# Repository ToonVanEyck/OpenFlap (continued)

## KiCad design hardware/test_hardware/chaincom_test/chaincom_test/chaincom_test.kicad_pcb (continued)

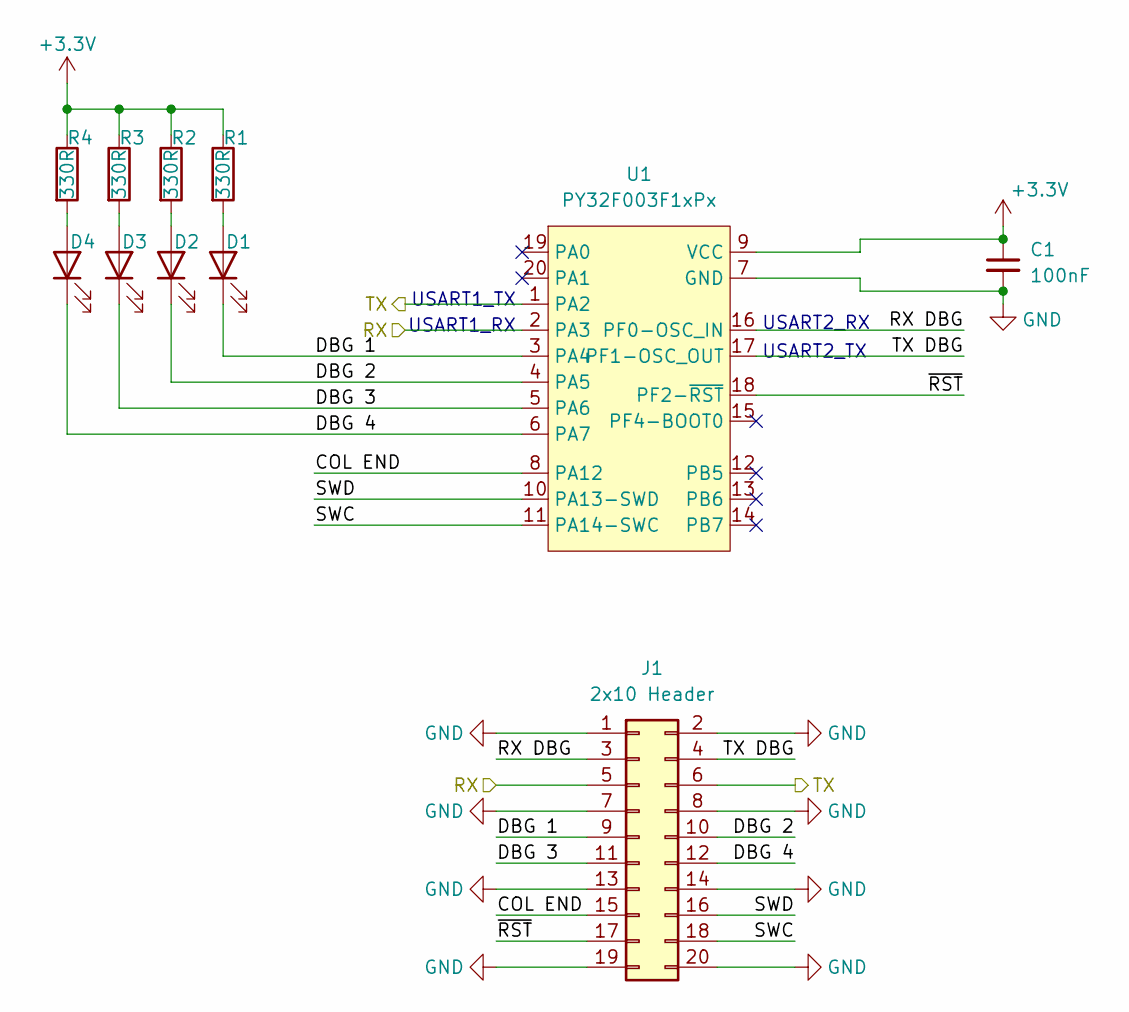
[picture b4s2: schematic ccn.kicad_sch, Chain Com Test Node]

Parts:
C1: 100nF; C_0805_2012Metric
D1: XL-1608UBC-06A; LED_0603_1608Metric; LCSC C7371904
D2: XL-1608SYGC-06; LED_0603_1608Metric; LCSC C965805
D3: XL-1608UOC-06; LED_0603_1608Metric; LCSC C965800
D4: XL-1608SURC-06; LED_0603_1608Metric; LCSC C965799
J1: 2x10 Header; PinHeader_2x10_P2.54mm_Vertical
R1, R2, R3, R4: 330R; R_0805_2012Metric
U1: PY32F003F1xPx; TSSOP-20_4.4x6.5mm_P0.65mm; LCSC C5379864

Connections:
+3.3V: C1.1, R1.1, R2.1, R3.1, R4.1, U1.9 (VCC); also elsewhere on the board
/Chain Com Node 1/COL END: J1.15, U1.8 (PA12)
/Chain Com Node 1/DBG 1: D1.1 (K), J1.9, U1.3 (PA4)
/Chain Com Node 1/DBG 2: D2.1 (K), J1.10, U1.4 (PA5)
/Chain Com Node 1/DBG 3: D3.1 (K), J1.11, U1.5 (PA6)
/Chain Com Node 1/DBG 4: D4.1 (K), J1.12, U1.6 (PA7)
/Chain Com Node 1/RX DBG: J1.3, U1.16 (PF0-OSC_IN)
/Chain Com Node 1/SWC: J1.18, U1.11 (PA14-SWC)
/Chain Com Node 1/SWD: J1.16, U1.10 (PA13-SWD)
/Chain Com Node 1/TX: J1.6, U1.1 (PA2); also elsewhere on the board
/Chain Com Node 1/TX DBG: J1.4, U1.17 (PF1-OSC_OUT)
/Chain Com Node 1/~RST: J1.17, U1.18 (PF2-~RST)
/TX To Module: J1.5, U1.2 (PA3); also elsewhere on the board
GND: C1.2, J1.1, J1.2, J1.7, J1.8, J1.13, J1.14, J1.19, J1.20, U1.7 (GND); also elsewhere on the board
unnamed: D1.2 (A), R1.2
unnamed: D2.2 (A), R2.2
unnamed: D3.2 (A), R3.2
unnamed: D4.2 (A), R4.2

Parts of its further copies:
C5, C6, C7, C8, C9, C10, C11, C12, C13, C14, C15, C16, C17, C18, C19: 100nF; C_0805_2012Metric
D5, D9, D13, D17, D21, D25, D29, D33, D37, D41, D45, D49, D53, D57, D61: XL-1608SURC-06; LED_0603_1608Metric; LCSC C965799
D6, D10, D14, D18, D22, D26, D30, D34, D38, D42, D46, D50, D54, D58, D62: XL-1608UOC-06; LED_0603_1608Metric; LCSC C965800
D7, D11, D15, D19, D23, D27, D31, D35, D39, D43, D47, D51, D55, D59, D63: XL-1608SYGC-06; LED_0603_1608Metric; LCSC C965805
D8, D12, D16, D20, D24, D28, D32, D36, D40, D44, D48, D52, D56, D60, D64: XL-1608UBC-06A; LED_0603_1608Metric; LCSC C7371904
J2, J3, J5, J6, J7, J8, J9, J10, J11, J12, J13, J14, J15, J16, J17: 2x10 Header; PinHeader_2x10_P2.54mm_Vertical
R5, R6, R7, R8, R9, R10, R11, R12, R13, R14, R15, R16, R17, R18, R19, R20, R21, R22, R23, R24, R25, R26, R27, R28, R29, R30, R31, R32, R33, R34, R35, R36, R37, R38, R39, R40, R41, R42, R43, R44, R45, R46, R47, R48, R49, R50, R51, R52, R53, R54, R55, R56, R57, R58, R59, R60, R61, R62, R63, R64: 330R; R_0805_2012Metric
U2, U3, U4, U5, U6, U7, U8, U9, U10, U11, U12, U13, U14, U15, U16: PY32F003F1xPx; TSSOP-20_4.4x6.5mm_P0.65mm; LCSC C5379864

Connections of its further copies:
+3.3V: C5.1, C6.1, C7.1, C8.1, C9.1, C10.1, C11.1, C12.1, C13.1, C14.1, C15.1, C16.1, C17.1, C18.1, C19.1, R5.1, R6.1, R7.1, R8.1, R9.1, R10.1, R11.1, R12.1, R13.1, R14.1, R15.1, R16.1, R17.1, R18.1, R19.1, R20.1, R21.1, R22.1, R23.1, R24.1, R25.1, R26.1, R27.1, R28.1, R29.1, R30.1, R31.1, R32.1, R33.1, R34.1, R35.1, R36.1, R37.1, R38.1, R39.1, R40.1, R41.1, R42.1, R43.1, R44.1, R45.1, R46.1, R47.1, R48.1, R49.1, R50.1, R51.1, R52.1, R53.1, R54.1, R55.1, R56.1, R57.1, R58.1, R59.1, R60.1, R61.1, R62.1, R63.1, R64.1, U2.9 (VCC), U3.9 (VCC), U4.9 (VCC), U5.9 (VCC), U6.9 (VCC), U7.9 (VCC), U8.9 (VCC), U9.9 (VCC), U10.9 (VCC), U11.9 (VCC), U12.9 (VCC), U13.9 (VCC), U14.9 (VCC), U15.9 (VCC), U16.9 (VCC); also elsewhere on the board
/Chain Com Node 1/TX: J2.5, U2.2 (PA3); also elsewhere on the board
/Chain Com Node 2/COL END: J2.15, U2.8 (PA12)
/Chain Com Node 2/DBG 1: D8.1 (K), J2.9, U2.3 (PA4)
/Chain Com Node 2/DBG 2: D7.1 (K), J2.10, U2.4 (PA5)
/Chain Com Node 2/DBG 3: D6.1 (K), J2.11, U2.5 (PA6)
/Chain Com Node 2/DBG 4: D5.1 (K), J2.12, U2.6 (PA7)
/Chain Com Node 2/RX DBG: J2.3, U2.16 (PF0-OSC_IN)
/Chain Com Node 2/SWC: J2.18, U2.11 (PA14-SWC)
/Chain Com Node 2/SWD: J2.16, U2.10 (PA13-SWD)
/Chain Com Node 2/TX: J2.6, J3.5, U2.1 (PA2), U3.2 (PA3)
/Chain Com Node 2/TX DBG: J2.4, U2.17 (PF1-OSC_OUT)
/Chain Com Node 2/~RST: J2.17, U2.18 (PF2-~RST)
/Chain Com Node 3/COL END: J3.15, U3.8 (PA12)
/Chain Com Node 3/DBG 1: D12.1 (K), J3.9, U3.3 (PA4)
/Chain Com Node 3/DBG 2: D11.1 (K), J3.10, U3.4 (PA5)
/Chain Com Node 3/DBG 3: D10.1 (K), J3.11, U3.5 (PA6)
/Chain Com Node 3/DBG 4: D9.1 (K), J3.12, U3.6 (PA7)
/Chain Com Node 3/RX DBG: J3.3, U3.16 (PF0-OSC_IN)
/Chain Com Node 3/SWC: J3.18, U3.11 (PA14-SWC)
/Chain Com Node 3/SWD: J3.16, U3.10 (PA13-SWD)
/Chain Com Node 3/TX: J3.6, J5.5, U3.1 (PA2), U4.2 (PA3)
/Chain Com Node 3/TX DBG: J3.4, U3.17 (PF1-OSC_OUT)
/Chain Com Node 3/~RST: J3.17, U3.18 (PF2-~RST)
/Chain Com Node 4/COL END: J5.15, U4.8 (PA12)
/Chain Com Node 4/DBG 1: D16.1 (K), J5.9, U4.3 (PA4)
/Chain Com Node 4/DBG 2: D15.1 (K), J5.10, U4.4 (PA5)
/Chain Com Node 4/DBG 3: D14.1 (K), J5.11, U4.5 (PA6)
/Chain Com Node 4/DBG 4: D13.1 (K), J5.12, U4.6 (PA7)
/Chain Com Node 4/RX DBG: J5.3, U4.16 (PF0-OSC_IN)
/Chain Com Node 4/SWC: J5.18, U4.11 (PA14-SWC)
/Chain Com Node 4/SWD: J5.16, U4.10 (PA13-SWD)
/Chain Com Node 4/TX: J5.6, J6.5, U4.1 (PA2), U5.2 (PA3)
/Chain Com Node 4/TX DBG: J5.4, U4.17 (PF1-OSC_OUT)
/Chain Com Node 4/~RST: J5.17, U4.18 (PF2-~RST)
/Chain Com Node 5/COL END: J6.15, U5.8 (PA12)
/Chain Com Node 5/DBG 1: D20.1 (K), J6.9, U5.3 (PA4)
/Chain Com Node 5/DBG 2: D19.1 (K), J6.10, U5.4 (PA5)
/Chain Com Node 5/DBG 3: D18.1 (K), J6.11, U5.5 (PA6)
/Chain Com Node 5/DBG 4: D17.1 (K), J6.12, U5.6 (PA7)
/Chain Com Node 5/RX DBG: J6.3, U5.16 (PF0-OSC_IN)
/Chain Com Node 5/SWC: J6.18, U5.11 (PA14-SWC)
/Chain Com Node 5/SWD: J6.16, U5.10 (PA13-SWD)
/Chain Com Node 5/TX: J6.6, J7.5, U5.1 (PA2), U6.2 (PA3)
/Chain Com Node 5/TX DBG: J6.4, U5.17 (PF1-OSC_OUT)
/Chain Com Node 5/~RST: J6.17, U5.18 (PF2-~RST)
/Chain Com Node 6/COL END: J7.15, U6.8 (PA12)
/Chain Com Node 6/DBG 1: D24.1 (K), J7.9, U6.3 (PA4)
/Chain Com Node 6/DBG 2: D23.1 (K), J7.10, U6.4 (PA5)
/Chain Com Node 6/DBG 3: D22.1 (K), J7.11, U6.5 (PA6)
/Chain Com Node 6/DBG 4: D21.1 (K), J7.12, U6.6 (PA7)
/Chain Com Node 6/RX DBG: J7.3, U6.16 (PF0-OSC_IN)
/Chain Com Node 6/SWC: J7.18, U6.11 (PA14-SWC)
/Chain Com Node 6/SWD: J7.16, U6.10 (PA13-SWD)
/Chain Com Node 6/TX: J7.6, J8.5, U6.1 (PA2), U7.2 (PA3)
/Chain Com Node 6/TX DBG: J7.4, U6.17 (PF1-OSC_OUT)
/Chain Com Node 6/~RST: J7.17, U6.18 (PF2-~RST)
/Chain Com Node 7/COL END: J8.15, U7.8 (PA12)
/Chain Com Node 7/DBG 1: D28.1 (K), J8.9, U7.3 (PA4)
/Chain Com Node 7/DBG 2: D27.1 (K), J8.10, U7.4 (PA5)
/Chain Com Node 7/DBG 3: D26.1 (K), J8.11, U7.5 (PA6)
/Chain Com Node 7/DBG 4: D25.1 (K), J8.12, U7.6 (PA7)
/Chain Com Node 7/RX DBG: J8.3, U7.16 (PF0-OSC_IN)
/Chain Com Node 7/SWC: J8.18, U7.11 (PA14-SWC)
/Chain Com Node 7/SWD: J8.16, U7.10 (PA13-SWD)
/Chain Com Node 7/TX: J8.6, J9.5, U7.1 (PA2), U8.2 (PA3)
/Chain Com Node 7/TX DBG: J8.4, U7.17 (PF1-OSC_OUT)
/Chain Com Node 7/~RST: J8.17, U7.18 (PF2-~RST)
/Chain Com Node 8/COL END: J9.15, U8.8 (PA12)
/Chain Com Node 8/DBG 1: D32.1 (K), J9.9, U8.3 (PA4)
/Chain Com Node 8/DBG 2: D31.1 (K), J9.10, U8.4 (PA5)
/Chain Com Node 8/DBG 3: D30.1 (K), J9.11, U8.5 (PA6)
/Chain Com Node 8/DBG 4: D29.1 (K), J9.12, U8.6 (PA7)
/Chain Com Node 8/RX DBG: J9.3, U8.16 (PF0-OSC_IN)
/Chain Com Node 8/SWC: J9.18, U8.11 (PA14-SWC)
/Chain Com Node 8/SWD: J9.16, U8.10 (PA13-SWD)
/Chain Com Node 8/TX: J9.6, J10.5, U8.1 (PA2), U9.2 (PA3)
/Chain Com Node 8/TX DBG: J9.4, U8.17 (PF1-OSC_OUT)
/Chain Com Node 8/~RST: J9.17, U8.18 (PF2-~RST)
/Chain Com Node 9/COL END: J10.15, U9.8 (PA12)
/Chain Com Node 9/DBG 1: D36.1 (K), J10.9, U9.3 (PA4)
/Chain Com Node 9/DBG 2: D35.1 (K), J10.10, U9.4 (PA5)
/Chain Com Node 9/DBG 3: D34.1 (K), J10.11, U9.5 (PA6)
/Chain Com Node 9/DBG 4: D33.1 (K), J10.12, U9.6 (PA7)
/Chain Com Node 9/RX DBG: J10.3, U9.16 (PF0-OSC_IN)
/Chain Com Node 9/SWC: J10.18, U9.11 (PA14-SWC)
/Chain Com Node 9/SWD: J10.16, U9.10 (PA13-SWD)
/Chain Com Node 9/TX DBG: J10.4, U9.17 (PF1-OSC_OUT)
/Chain Com Node 9/~RST: J10.17, U9.18 (PF2-~RST)
/Chain Com Node 10/COL END: J11.15, U10.8 (PA12)
/Chain Com Node 10/DBG 1: D40.1 (K), J11.9, U10.3 (PA4)
/Chain Com Node 10/DBG 2: D39.1 (K), J11.10, U10.4 (PA5)
/Chain Com Node 10/DBG 3: D38.1 (K), J11.11, U10.5 (PA6)
/Chain Com Node 10/DBG 4: D37.1 (K), J11.12, U10.6 (PA7)
/Chain Com Node 10/RX: J10.6, J11.5, U9.1 (PA2), U10.2 (PA3)
/Chain Com Node 10/RX DBG: J11.3, U10.16 (PF0-OSC_IN)
/Chain Com Node 10/SWC: J11.18, U10.11 (PA14-SWC)
/Chain Com Node 10/SWD: J11.16, U10.10 (PA13-SWD)
/Chain Com Node 10/TX: J11.6, J12.5, U10.1 (PA2), U11.2 (PA3)
/Chain Com Node 10/TX DBG: J11.4, U10.17 (PF1-OSC_OUT)
/Chain Com Node 10/~RST: J11.17, U10.18 (PF2-~RST)
/Chain Com Node 11/COL END: J12.15, U11.8 (PA12)
/Chain Com Node 11/DBG 1: D44.1 (K), J12.9, U11.3 (PA4)
/Chain Com Node 11/DBG 2: D43.1 (K), J12.10, U11.4 (PA5)
/Chain Com Node 11/DBG 3: D42.1 (K), J12.11, U11.5 (PA6)
/Chain Com Node 11/DBG 4: D41.1 (K), J12.12, U11.6 (PA7)
/Chain Com Node 11/RX DBG: J12.3, U11.16 (PF0-OSC_IN)
/Chain Com Node 11/SWC: J12.18, U11.11 (PA14-SWC)
/Chain Com Node 11/SWD: J12.16, U11.10 (PA13-SWD)
/Chain Com Node 11/TX: J12.6, J13.5, U11.1 (PA2), U12.2 (PA3)
/Chain Com Node 11/TX DBG: J12.4, U11.17 (PF1-OSC_OUT)
/Chain Com Node 11/~RST: J12.17, U11.18 (PF2-~RST)
/Chain Com Node 12/COL END: J13.15, U12.8 (PA12)
/Chain Com Node 12/DBG 1: D48.1 (K), J13.9, U12.3 (PA4)
/Chain Com Node 12/DBG 2: D47.1 (K), J13.10, U12.4 (PA5)
/Chain Com Node 12/DBG 3: D46.1 (K), J13.11, U12.5 (PA6)
/Chain Com Node 12/DBG 4: D45.1 (K), J13.12, U12.6 (PA7)
/Chain Com Node 12/RX DBG: J13.3, U12.16 (PF0-OSC_IN)
/Chain Com Node 12/SWC: J13.18, U12.11 (PA14-SWC)
/Chain Com Node 12/SWD: J13.16, U12.10 (PA13-SWD)
/Chain Com Node 12/TX: J13.6, J14.5, U12.1 (PA2), U13.2 (PA3)
/Chain Com Node 12/TX DBG: J13.4, U12.17 (PF1-OSC_OUT)
/Chain Com Node 12/~RST: J13.17, U12.18 (PF2-~RST)
/Chain Com Node 13/COL END: J14.15, U13.8 (PA12)
/Chain Com Node 13/DBG 1: D52.1 (K), J14.9, U13.3 (PA4)
/Chain Com Node 13/DBG 2: D51.1 (K), J14.10, U13.4 (PA5)
/Chain Com Node 13/DBG 3: D50.1 (K), J14.11, U13.5 (PA6)
/Chain Com Node 13/DBG 4: D49.1 (K), J14.12, U13.6 (PA7)
/Chain Com Node 13/RX DBG: J14.3, U13.16 (PF0-OSC_IN)
/Chain Com Node 13/SWC: J14.18, U13.11 (PA14-SWC)
/Chain Com Node 13/SWD: J14.16, U13.10 (PA13-SWD)
/Chain Com Node 13/TX: J14.6, J15.5, U13.1 (PA2), U14.2 (PA3)
/Chain Com Node 13/TX DBG: J14.4, U13.17 (PF1-OSC_OUT)
/Chain Com Node 13/~RST: J14.17, U13.18 (PF2-~RST)
/Chain Com Node 14/COL END: J15.15, U14.8 (PA12)
/Chain Com Node 14/DBG 1: D56.1 (K), J15.9, U14.3 (PA4)
/Chain Com Node 14/DBG 2: D55.1 (K), J15.10, U14.4 (PA5)
/Chain Com Node 14/DBG 3: D54.1 (K), J15.11, U14.5 (PA6)
/Chain Com Node 14/DBG 4: D53.1 (K), J15.12, U14.6 (PA7)
/Chain Com Node 14/RX DBG: J15.3, U14.16 (PF0-OSC_IN)
/Chain Com Node 14/SWC: J15.18, U14.11 (PA14-SWC)
/Chain Com Node 14/SWD: J15.16, U14.10 (PA13-SWD)
/Chain Com Node 14/TX: J15.6, J16.5, U14.1 (PA2), U15.2 (PA3)
/Chain Com Node 14/TX DBG: J15.4, U14.17 (PF1-OSC_OUT)
/Chain Com Node 14/~RST: J15.17, U14.18 (PF2-~RST)
/Chain Com Node 15/COL END: J16.15, U15.8 (PA12)
/Chain Com Node 15/DBG 1: D60.1 (K), J16.9, U15.3 (PA4)
/Chain Com Node 15/DBG 2: D59.1 (K), J16.10, U15.4 (PA5)
/Chain Com Node 15/DBG 3: D58.1 (K), J16.11, U15.5 (PA6)
/Chain Com Node 15/DBG 4: D57.1 (K), J16.12, U15.6 (PA7)
/Chain Com Node 15/RX DBG: J16.3, U15.16 (PF0-OSC_IN)
/Chain Com Node 15/SWC: J16.18, U15.11 (PA14-SWC)
/Chain Com Node 15/SWD: J16.16, U15.10 (PA13-SWD)
/Chain Com Node 15/TX: J16.6, J17.5, U15.1 (PA2), U16.2 (PA3)
/Chain Com Node 15/TX DBG: J16.4, U15.17 (PF1-OSC_OUT)
/Chain Com Node 15/~RST: J16.17, U15.18 (PF2-~RST)
/Chain Com Node 16/COL END: J17.15, U16.8 (PA12)
/Chain Com Node 16/DBG 1: D64.1 (K), J17.9, U16.3 (PA4)
/Chain Com Node 16/DBG 2: D63.1 (K), J17.10, U16.4 (PA5)
/Chain Com Node 16/DBG 3: D62.1 (K), J17.11, U16.5 (PA6)
/Chain Com Node 16/DBG 4: D61.1 (K), J17.12, U16.6 (PA7)
/Chain Com Node 16/RX DBG: J17.3, U16.16 (PF0-OSC_IN)
/Chain Com Node 16/SWC: J17.18, U16.11 (PA14-SWC)
/Chain Com Node 16/SWD: J17.16, U16.10 (PA13-SWD)
/Chain Com Node 16/TX DBG: J17.4, U16.17 (PF1-OSC_OUT)
/Chain Com Node 16/~RST: J17.17, U16.18 (PF2-~RST)
/RX From Module: J17.6, U16.1 (PA2); also elsewhere on the board
GND: C5.2, C6.2, C7.2, C8.2, C9.2, C10.2, C11.2, C12.2, C13.2, C14.2, C15.2, C16.2, C17.2, C18.2, C19.2, J2.1, J2.2, J2.7, J2.8, J2.13, J2.14, J2.19, J2.20, J3.1, J3.2, J3.7, J3.8, J3.13, J3.14, J3.19, J3.20, J5.1, J5.2, J5.7, J5.8, J5.13, J5.14, J5.19, J5.20, J6.1, J6.2, J6.7, J6.8, J6.13, J6.14, J6.19, J6.20, J7.1, J7.2, J7.7, J7.8, J7.13, J7.14, J7.19, J7.20, J8.1, J8.2, J8.7, J8.8, J8.13, J8.14, J8.19, J8.20, J9.1, J9.2, J9.7, J9.8, J9.13, J9.14, J9.19, J9.20, J10.1, J10.2, J10.7, J10.8, J10.13, J10.14, J10.19, J10.20, J11.1, J11.2, J11.7, J11.8, J11.13, J11.14, J11.19, J11.20, J12.1, J12.2, J12.7, J12.8, J12.13, J12.14, J12.19, J12.20, J13.1, J13.2, J13.7, J13.8, J13.13, J13.14, J13.19, J13.20, J14.1, J14.2, J14.7, J14.8, J14.13, J14.14, J14.19, J14.20, J15.1, J15.2, J15.7, J15.8, J15.13, J15.14, J15.19, J15.20, J16.1, J16.2, J16.7, J16.8, J16.13, J16.14, J16.19, J16.20, J17.1, J17.2, J17.7, J17.8, J17.13, J17.14, J17.19, J17.20, U2.7 (GND), U3.7 (GND), U4.7 (GND), U5.7 (GND), U6.7 (GND), U7.7 (GND), U8.7 (GND), U9.7 (GND), U10.7 (GND), U11.7 (GND), U12.7 (GND), U13.7 (GND), U14.7 (GND), U15.7 (GND), U16.7 (GND); also elsewhere on the board
unnamed: D5.2 (A), R5.2
unnamed: D6.2 (A), R6.2
unnamed: D7.2 (A), R7.2
unnamed: D8.2 (A), R8.2
unnamed: D9.2 (A), R9.2
unnamed: D10.2 (A), R10.2
unnamed: D11.2 (A), R11.2
unnamed: D12.2 (A), R12.2
unnamed: D13.2 (A), R13.2
unnamed: D14.2 (A), R14.2
unnamed: D15.2 (A), R15.2
unnamed: D16.2 (A), R16.2
unnamed: D17.2 (A), R17.2
unnamed: D18.2 (A), R18.2
unnamed: D19.2 (A), R19.2
unnamed: D20.2 (A), R20.2
unnamed: D21.2 (A), R21.2
unnamed: D22.2 (A), R22.2
unnamed: D23.2 (A), R23.2
unnamed: D24.2 (A), R24.2
unnamed: D25.2 (A), R25.2
unnamed: D26.2 (A), R26.2
unnamed: D27.2 (A), R27.2
unnamed: D28.2 (A), R28.2
unnamed: D29.2 (A), R29.2
unnamed: D30.2 (A), R30.2
unnamed: D31.2 (A), R31.2
unnamed: D32.2 (A), R32.2
unnamed: D33.2 (A), R33.2
unnamed: D34.2 (A), R34.2
unnamed: D35.2 (A), R35.2
unnamed: D36.2 (A), R36.2
unnamed: D37.2 (A), R37.2
unnamed: D38.2 (A), R38.2
unnamed: D39.2 (A), R39.2
unnamed: D40.2 (A), R40.2
unnamed: D41.2 (A), R41.2
unnamed: D42.2 (A), R42.2
unnamed: D43.2 (A), R43.2
unnamed: D44.2 (A), R44.2
unnamed: D45.2 (A), R45.2
unnamed: D46.2 (A), R46.2
unnamed: D47.2 (A), R47.2
unnamed: D48.2 (A), R48.2
unnamed: D49.2 (A), R49.2
unnamed: D50.2 (A), R50.2
unnamed: D51.2 (A), R51.2
unnamed: D52.2 (A), R52.2
unnamed: D53.2 (A), R53.2
unnamed: D54.2 (A), R54.2
unnamed: D55.2 (A), R55.2
unnamed: D56.2 (A), R56.2
unnamed: D57.2 (A), R57.2
unnamed: D58.2 (A), R58.2
unnamed: D59.2 (A), R59.2
unnamed: D60.2 (A), R60.2
unnamed: D61.2 (A), R61.2
unnamed: D62.2 (A), R62.2
unnamed: D63.2 (A), R63.2
unnamed: D64.2 (A), R64.2

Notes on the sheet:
USART2_RX
USART2_TX
USART1_RX
USART1_TX

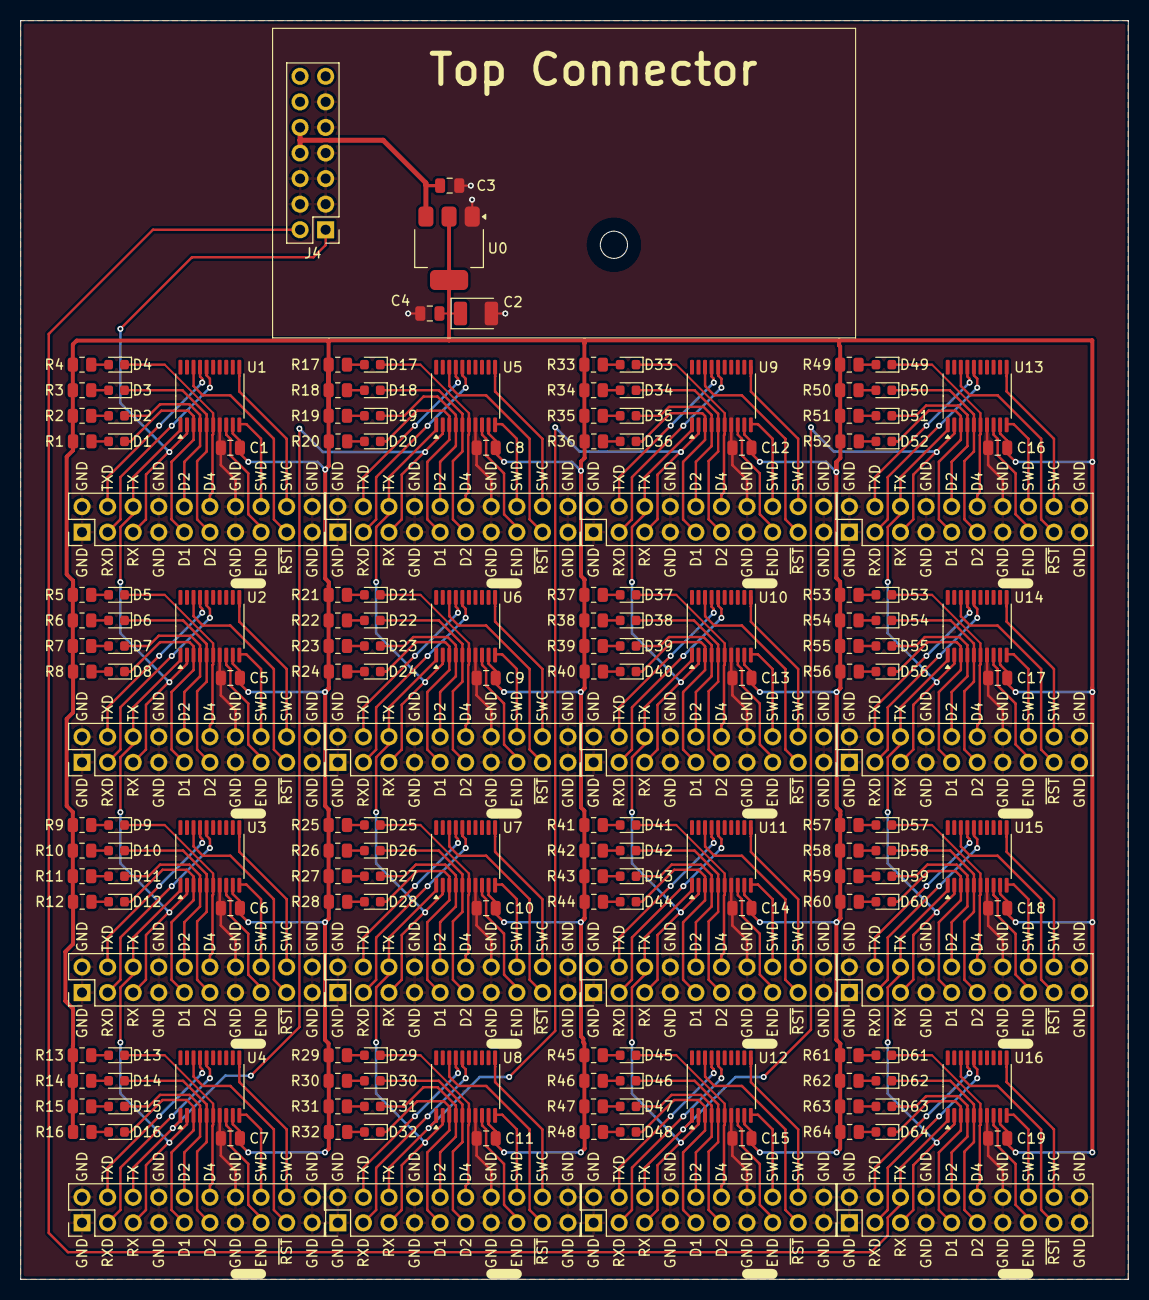
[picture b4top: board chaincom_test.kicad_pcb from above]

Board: 2 copper layers, 110.0 x 125.0 mm, 182 parts (0 on the bottom side), 245 nets.

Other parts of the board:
H1: (no value)

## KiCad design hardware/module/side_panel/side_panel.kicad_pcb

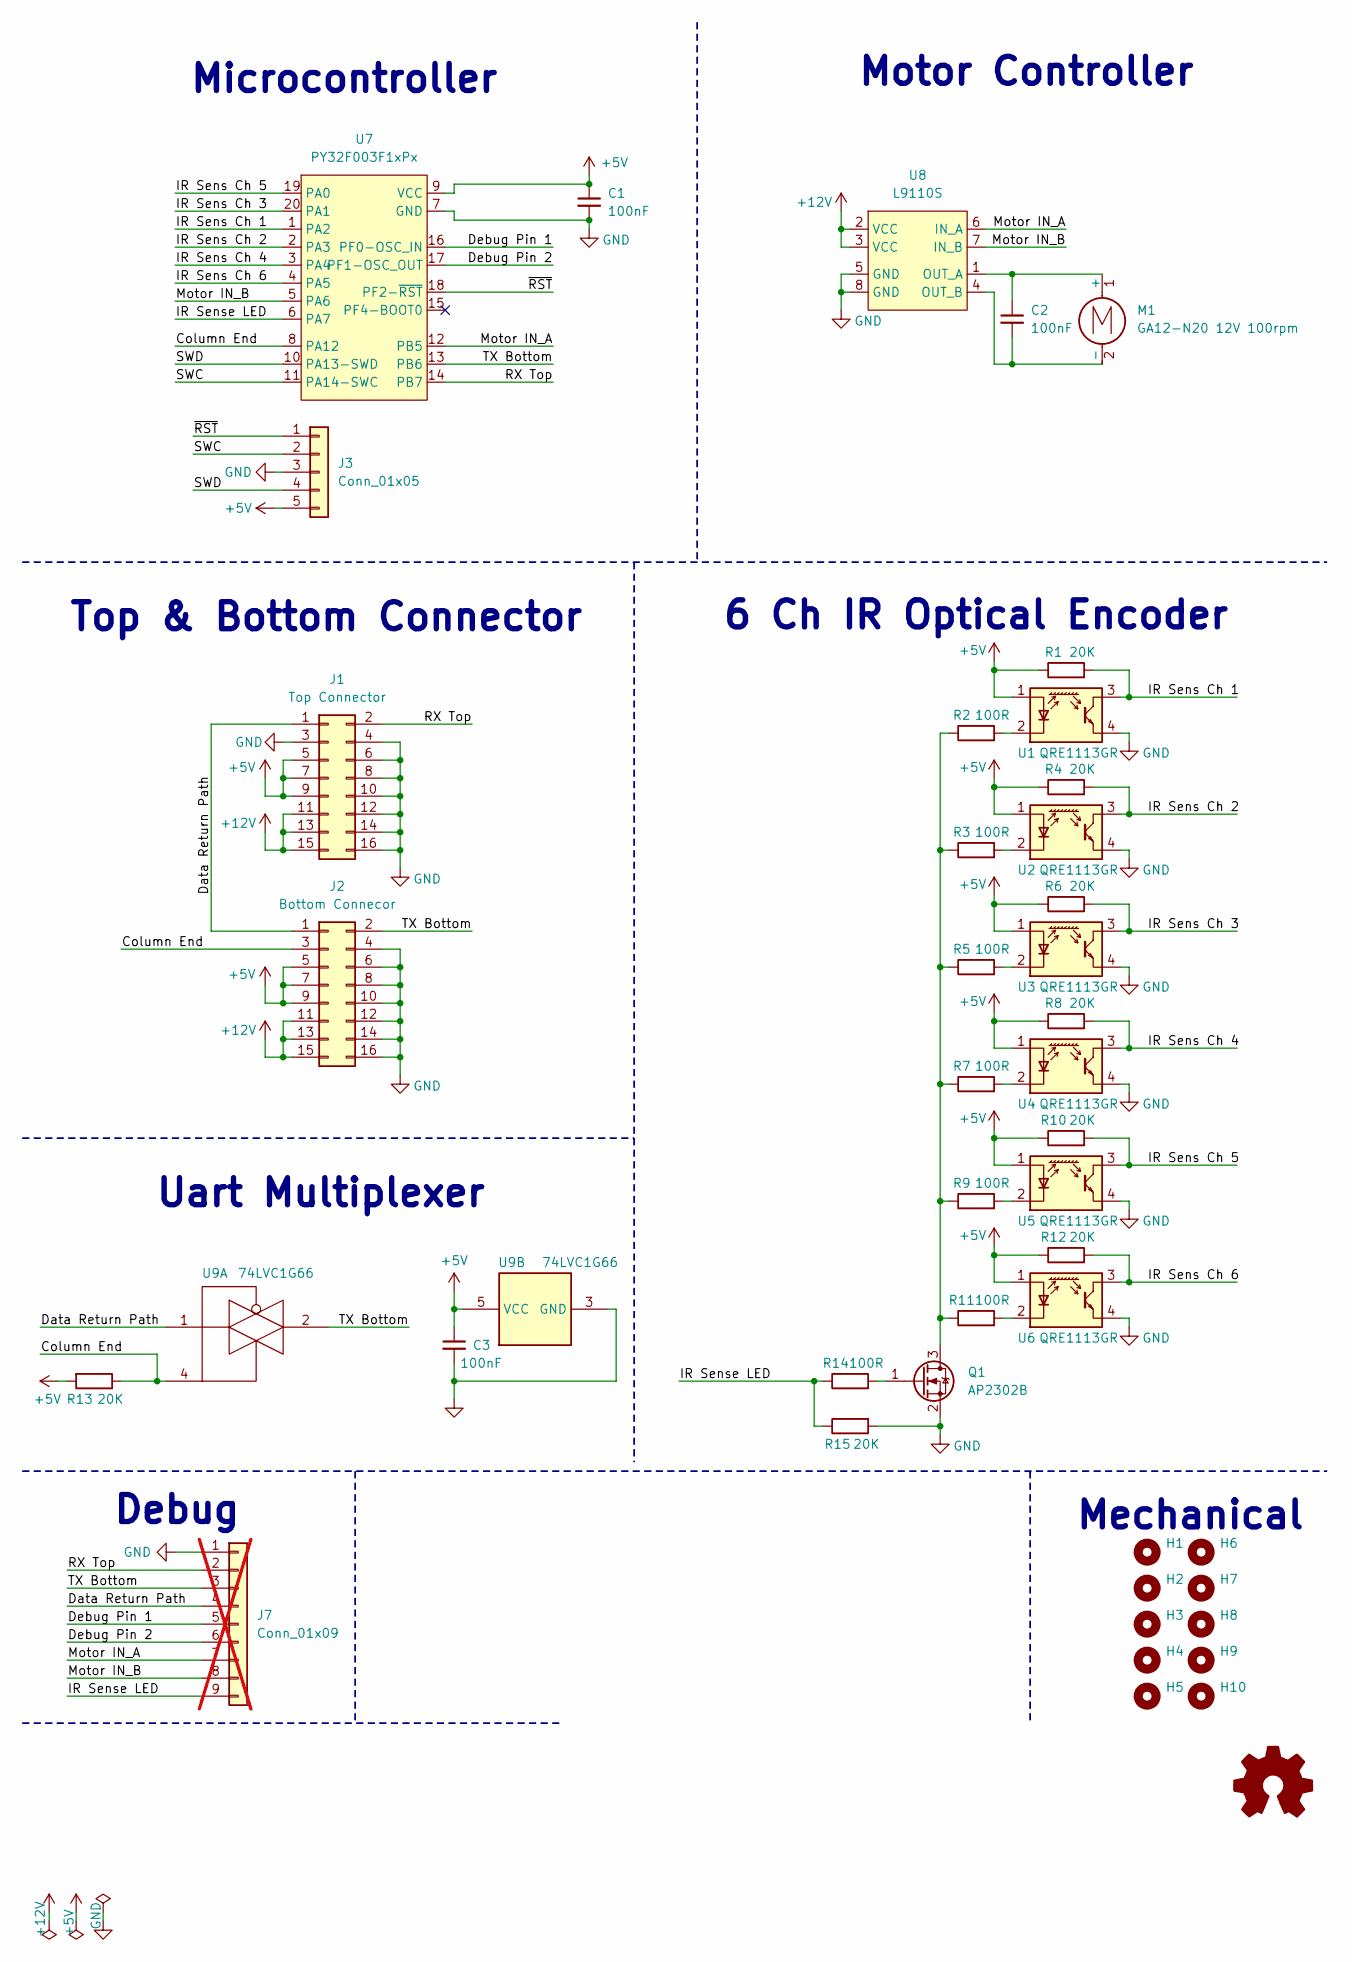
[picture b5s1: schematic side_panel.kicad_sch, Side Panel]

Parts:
C1, C2, C3: 100nF; C_0805_2012Metric
H1, H2, H3, H4, H5, H6, H7, H8, H9, H10: MountingHole; MountingHole_2.7mm_M2.5_ISO14580
J1: Top Connector; PinHeader_2x08_P2.54mm_Horizontal; LCSC C358710
J2: Bottom Connecor; PinSocket_2x08_P2.54mm_Horizontal; LCSC C239359
J3: Conn_01x05; PinHeader_1x05_P2.54mm_Vertical
J7: Conn_01x09; PinHeader_1x09_P2.54mm_Vertical; not fitted
M1: GA12-N20 12V 100rpm; GA12-N20 Motor Vertical
Q1: AP2302B; SOT-23; LCSC C406812
R1, R4, R6, R8, R10, R12, R13, R15: 20K; R_0805_2012Metric
R2, R3, R5, R7, R9, R11, R14: 100R; R_0805_2012Metric
U1, U2, U3, U4, U5, U6: QRE1113GR; OnSemi_CASE100CY; LCSC C81632
U7: PY32F003F1xPx; TSSOP-20_4.4x6.5mm_P0.65mm; LCSC C5379864
U8: L9110S; SOP-8_3.76x4.96mm_P1.27mm; LCSC C2984833
U9: 74LVC1G66; SOT-23-5; LCSC C5375974

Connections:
+5V: C1.1, C3.1, J1.5, J1.7, J1.9, J2.5, J2.7, J2.9, J3.5, R1.1, R4.1, R6.1, R8.1, R10.1, R12.1, R13.2, U1.1 (A), U2.1 (A), U3.1 (A), U4.1 (A), U5.1 (A), U6.1 (A), U7.9 (VCC), U9.5 (VCC)
+12V: J1.11, J1.13, J1.15, J2.11, J2.13, J2.15, U8.2 (VCC), U8.3 (VCC)
/Column End: J2.3, R13.1, U7.8 (PA12), U9.4
/Data Return Path: J1.1, J2.1, J7.4, U9.1
/Debug Pin 1: J7.5, U7.16 (PF0-OSC_IN)
/Debug Pin 2: J7.6, U7.17 (PF1-OSC_OUT)
/IR Sens Ch 1: R1.2, U1.3, U7.1 (PA2)
/IR Sens Ch 2: R4.2, U2.3, U7.2 (PA3)
/IR Sens Ch 3: R6.2, U3.3, U7.20 (PA1)
/IR Sens Ch 4: R8.2, U4.3, U7.3 (PA4)
/IR Sens Ch 5: R10.2, U5.3, U7.19 (PA0)
/IR Sens Ch 6: R12.2, U6.3, U7.4 (PA5)
/IR Sense LED: J7.9, R14.1, R15.1, U7.6 (PA7)
/Motor IN_A: J7.7, U7.12 (PB5), U8.6 (IN_A)
/Motor IN_B: J7.8, U7.5 (PA6), U8.7 (IN_B)
/RX Top: J1.2, J7.2, U7.14 (PB7)
/SWC: J3.2, U7.11 (PA14-SWC)
/SWD: J3.4, U7.10 (PA13-SWD)
/TX Bottom: J2.2, J7.3, U7.13 (PB6), U9.2
/~RST: J3.1, U7.18 (PF2-~RST)
GND: C1.2, C3.2, J1.3, J1.4, J1.6, J1.8, J1.10, J1.12, J1.14, J1.16, J2.4, J2.6, J2.8, J2.10, J2.12, J2.14, J2.16, J3.3, J7.1, Q1.2 (S), R15.2, U1.4, U2.4, U3.4, U4.4, U5.4, U6.4, U7.7 (GND), U8.5 (GND), U8.8 (GND), U9.3 (GND)
unnamed: C2.1, M1.1 (+), U8.1 (OUT_A)
unnamed: C2.2, M1.2 (-), U8.4 (OUT_B)
unnamed: Q1.3 (D), R2.1, R3.1, R5.1, R7.1, R9.1, R11.1
unnamed: Q1.1 (G), R14.2
unnamed: R2.2, U1.2 (K)
unnamed: R3.2, U2.2 (K)
unnamed: R5.2, U3.2 (K)
unnamed: R7.2, U4.2 (K)
unnamed: R9.2, U5.2 (K)
unnamed: R11.2, U6.2 (K)

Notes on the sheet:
Top & Bottom Connector
6 Ch IR Optical Encoder
Uart Multiplexer
Motor Controller
Mechanical
Microcontroller
Debug

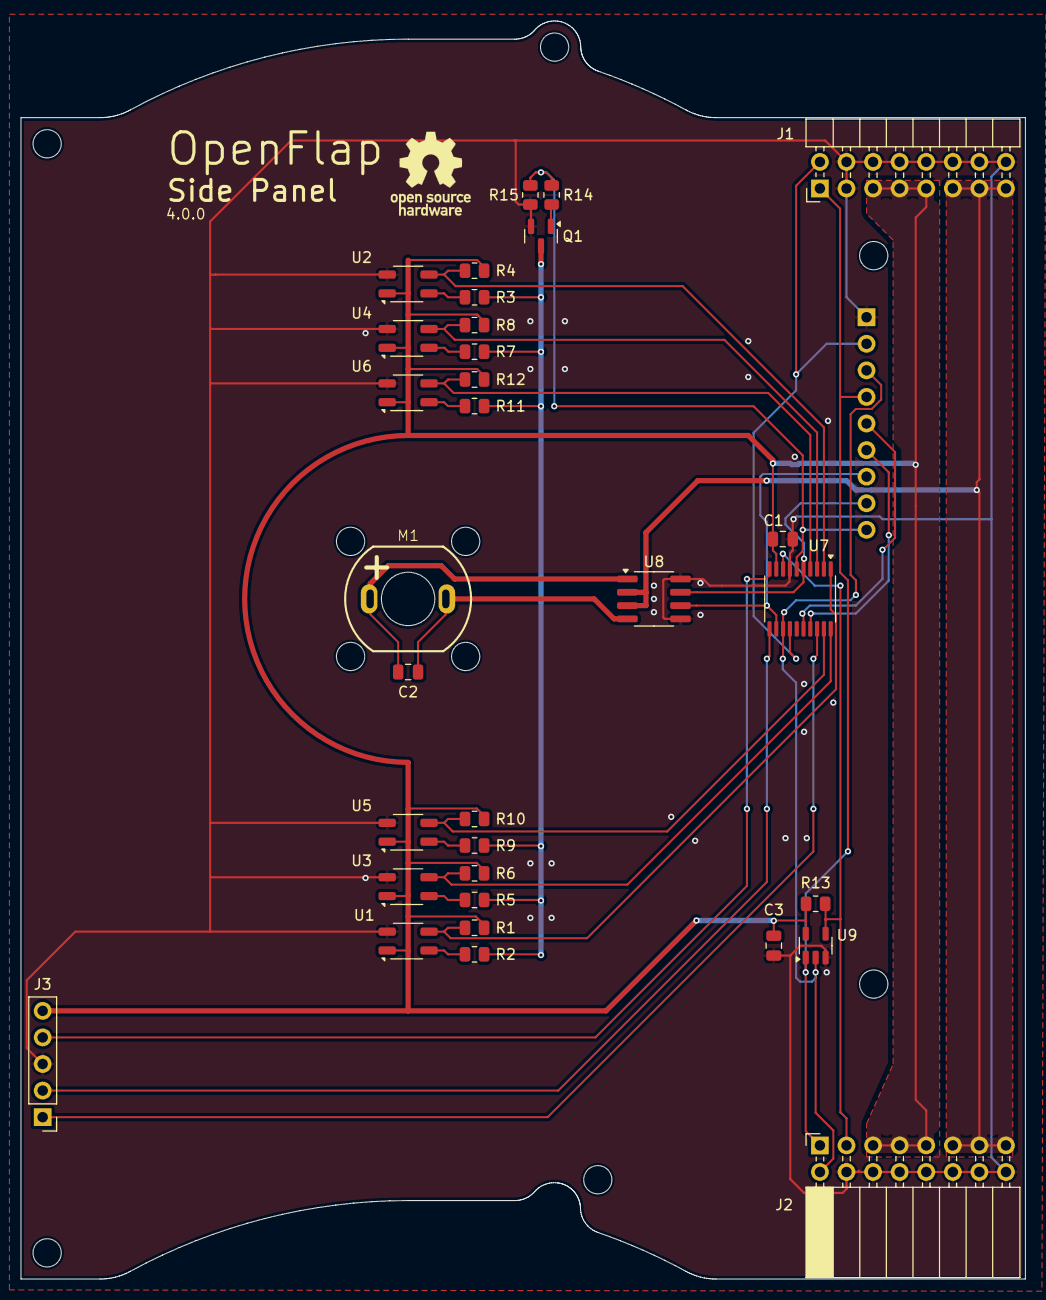
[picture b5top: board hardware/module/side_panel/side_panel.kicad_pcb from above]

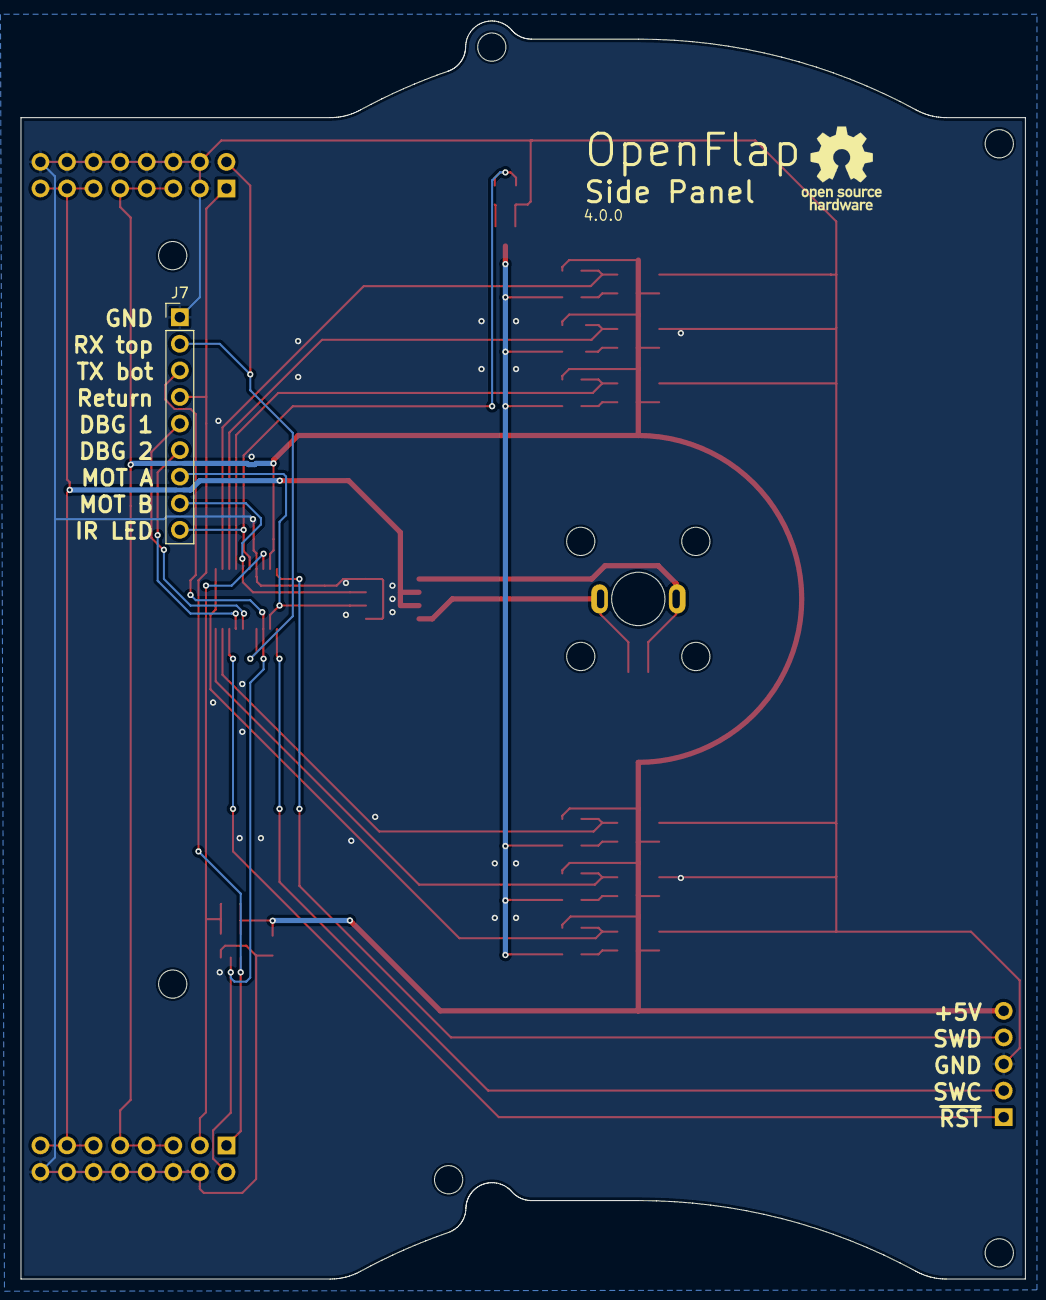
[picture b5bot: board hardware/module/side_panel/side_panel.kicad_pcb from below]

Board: 2 copper layers, 96.0 x 120.2 mm, 45 parts (2 on the bottom side), 31 nets.

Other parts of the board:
OSHW-LOGO-1, OSHW-LOGO-2: OSHW-Logo_7.5x8mm_SilkScreen

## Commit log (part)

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2022-04-25 Fixed typo
2022-04-25 added uart protocol description to README.md
2022-04-25 added 3d printing mesh files for modules
2022-04-25 changed 3mf files to stl files for better support on github.
2022-04-27 updated wiring svg
2022-04-27 replaced wiring diagram with by png
2022-04-27 Added linkes to 3d designs and pcb designs
2022-04-28 Added POC video
2022-05-02 Converted the old websocket based interface to a proper REST api.
2022-05-03 fixed bug causing corruped encoder offsets in modules
2022-05-03 Cleanup of encoder reading in module code
2022-05-03 tweeked pwm table to account for chnage from 100rpm to 60 rpm motor
2022-05-03 Fixed module initialization so the don't start on boot.
2022-05-05 Added script and other resources for procedurally generating flap PCB production files (gerbers) with inkscape and eagle.
2022-05-09 updated gitignore
2022-05-12 Added production files for controller, top-con and flap.
2022-05-13 Some code cleanup work
2022-05-13 Added module production files
2022-05-16 added statistics api with revolution counter but disabled the volatile storage for the rev counter.
2022-05-16 store revolution counter in nvm
2022-05-17 implemented a more complete version api. vesrion is shown as generated by ```git describe --tags --dirty=*```
2022-05-23 fixed issue in web page caused by scrollbar
2022-05-24 fixed issue in webpage caused by typo and some cleanup
2022-05-24 major cleanup/rework of module firmware. The firmware now executes at fixed tick rate of 10kHz
2022-05-24 fixed issue in cmake firmware version generation
2022-05-24 Fixed proper initialization of webpage through api calls. Added loader indicator.
2022-05-26 Added vtrim command and added increment and decrement mode to offset. No support for controller yet.
2022-05-31 reactivated revolution counter
2023-01-06 Added support for doing a complete revolution by sending a newline character.
2023-01-06 UI improvements
2023-01-06 Updated controller api to include vtrim en offset getters and removed statistics api
2023-06-27 Major rework of the controller and module communication. Rework of webpage. Reworked module properties.
2023-07-15 Added a devcontainer supporting ESP-IDF 5.1. Fixed a bug in the offset and vtrim module view.
2023-07-15 Add back removed files
2023-07-22 added eagle schematics and boards
2023-07-25 Updated the flap generations scripts to provide better gerber files for JLCPCB, ToDo: generate new flaps.
2023-07-25 Added new flap PCB production files
2023-08-02 Redrawn the 3d printed parts.
2023-08-02 Updated top-con board to use only one screw and improved the screw location
2023-09-13 Fix: Setting character map entries was broken.
2023-09-20 Fixed bug in json respons from controller
2024-03-21 started porting to py32f003 based module
2024-03-27 finished chaincomm FSM
2024-03-29 Added property handlers
2024-03-31 minor fixes
2024-04-04 fixed chaincomm and flash storage
2024-04-05 Added default configuration
2024-04-14 update cmake structure
2024-04-14 add addresses to flash functions
2024-04-20 Start work on bootloader
2024-04-22 implement jump to app function
2024-04-26 improved bootloader
2024-04-30 fix broken interrupts in app because of bootloader
2024-05-07 removed PIC firmware, module will use an ARM
2024-06-02 intermediate commit, working on ota
2024-06-08 Fixed bootloader
2024-06-09 add ir sensor adc calibration over rtt
2024-06-19 Fixed issues with the communication protocol and added random IR sensor offset and random seed generation.
2024-07-21 major rework of the communication and uart driver
2024-07-23 disable RTT debugging while communications a re ongoing as they might prevent the uart interrupt
2024-07-27 Switching to KiCad: Added top connector schematic and board
2024-08-19 initial commit: work in progress
2024-08-20 update flap template
2024-08-20 add flap destructor
2024-08-20 Add support for exporting and loading project as json. Redesign frontend using bootstrap (WIP)
2024-09-05 create default set and readme
2024-09-05 replace old flap dir with v2
2024-09-05 Add screenshot of flap generator
2024-09-05 Minor fixes to flap generator
2024-09-06 add workflow for generating pdf's from schematic
2024-09-06 test pr
2024-09-06 Workflow: Generate KiCad files
2024-09-11 splitting devcontainers, added devcontainer for kibot testing
2024-09-14 split devcontainer into 3 containers
2024-09-16 Use kibot on sidepanel and top connector
2024-09-20 set fetch depth in workflow
2024-09-21 Fix workflow
2024-09-25 fix typos
2024-10-03 Add FreeCad model and update board layout.
2024-10-03 install git lfs ind evcontainers
2024-10-11 Add script to exptort stl files from freecad
2024-10-16 Add workflow for validating Freecad Design
2024-10-16 enable lfs in github action
2024-10-16 make build dir
2024-10-18 Add support for directional motor control and braking
2024-10-18 tune default ramp
2024-10-22 improved core printability
2024-10-22 update puya docker
2024-10-22 add support for minimum rotation distance
2024-10-22 update gerbolyzer ci script to build out of source
2024-10-23 create encoder wheel in kicad
2024-12-27 Remade controller hardware in KiCad.
2024-12-28 Added TVS diode to UART line on side pannel
2024-12-28 Changed micro symbol to uF
2024-12-29 ad bash completion to kibot container
2024-12-29 hardware/resources/DC_JACK_SMT.stp: convert to Git LFS
2024-12-29 add a case for the controller
2024-12-30 added blender renderes to kibot
2025-01-01 Updated controller footprint and added testpads
2025-01-01 Added LCSC part number for esp32
2025-01-10 docs/images/browser_based_flap_generator.png,docs/images/controller.png,docs/images/flap_assembler.png,docs/images/flap_controller.png,docs/images/module.png,docs/images/signalpath.png,docs/images/to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
2025-01-16 Make FreeCad CI script callable from root
2025-01-16 rename some vars in ci script
2025-01-16 offset encoder pattern so inner trace does not line up with fasteners
2025-01-16 reverse motor polarity on side pannel
2025-01-16 add option to only run the kicad ci script for modified boards.
2025-01-16 added oled_disp component
2025-01-16 Added support for OLED display
2025-01-16 wip oled stuff
2025-01-16 experimenting with testing
2025-01-16 refactor: improve error handling and update message structures in chain communication
2025-01-16 change permissions
2025-01-16 attempt at compile time handler registration with linker fragment section
2025-01-16 fix resize bug causing crashes when resizing to zero
2025-01-16 Bring webserver up to date to switch to new api format
2025-01-16 add beginnings of controller OTA
2025-01-16 implemented writing dynamic length properties and fixed bug in rbuff
2025-01-21 Implement exporting of flap svg to stl file.
2025-01-21 remove magic numbers
2025-01-24 increase color thickness on 3d printed flaps
2025-01-24 remove print statements
2025-01-25 Fix position of characters which do not touch top edge of flap.
2025-01-26 fix: flip front and back of 3d printed flaps
2025-01-28 update side panel schematic motor RPM
2025-01-28 docs: add doc for running devcontainers using devcontainer cli
2025-01-29 reduce flap wheel side to side tolerance
2025-02-01 finish chain com module ota
2025-02-01 Add support for WriteSeq chain com command
2025-02-01 check display size when uploading module firmware
2025-02-01 finish up module OTA
2025-02-01 fix chain com read all dynamic size not working for consecutive modules
2025-02-01 start implementing firmware property for module ota
2025-02-01 add debug pin wiggling to side pannel
2025-02-01 Add short backspin to align lock flap against the latch.
2025-02-02 shrink top 0.5mm and reduce retainer thickness by .25mm
2025-02-02 minor tweaks
2025-02-02 rename controller_v2 to controller
2025-02-02 improved ir encoder response time
2025-02-03 remove test file
2025-02-03 update github actions for new devcontainers
2025-02-03 add mdns support
2025-02-09 encoder changes
2025-02-10 changed hole patern encoder wheel
2025-02-11 update pcb model in cad design
2025-02-12 rework properties wip
2025-02-15 added properties to controller (untested)
2025-02-18 Increase encoder LED current to 70mA and make make two pairs of 3 to reduce power draw
2025-02-27 fix pipeline
2025-02-28 Update github actions
2025-03-03 Setup formatting and codespell
2025-03-06 Update openflap module to use incremental encoder
2025-03-07 change latch position and geometry
2025-03-07 Side panel 5.0.1 swap motor polarity
2025-03-08 Start homing on boot and prevent flippering between 1 and 0.
2025-03-09 working on docs
2025-03-12 Fixed reworked properties
2025-03-26 Rework controller webpage for setting module properties
2025-03-27 increase hub and core CAD tolerances to reduce friction
2025-03-27 Add motor mode with breaking in order to slow down
2025-03-29 Fix module startup calibration.
2025-03-29 fix, send reboot command after module OTA in proper sequence
2025-03-29 update top connector to improve current path
2025-04-25 Add french cleat mounting system
2025-04-25 Fix broken flap to 3d script
2025-04-27 sepper 4 step
2025-04-27 stepper experiments
2025-04-28 Change CAD design to work with 35mm stepper motor
2025-05-17 Create proper stepper driver.
2025-07-10 Add simple ota script to bulk update the modules and provide immediate feedback based on CRC matching
2025-07-23 Implemented position pid, but considering speed pid instead...
2025-07-31 Rework top connector and side panel connections to increase power rating. Switch from 2 channel to 4 channel incremental encoder.
2025-08-02 Update side panel to add proper ESD protection, 12V detection, removed uart switch in favor of software switching, shuffled around some IO for improved routing.
2025-08-02 Reduced PWM frequency decrease switching losses in h-bride.
2025-08-23 side panel v7
2025-08-27 rework sidepanel to 3 sensors, ad 12V ok signal, add debug uart, change test points for skedd connector
2025-09-01 Fixed OTA, Added checksum to chain comm
2025-09-08 Change idle motor state from brake to freewheel to reduce power consumption.
2025-09-08 Optimize flap latch shape.
2025-09-15 Fix synchronization issue between controller and modules
2025-09-15 Update OTA ui logic
2025-09-16 Added logger to web UI but it's jank because I suck at html & css
2025-09-16 Fix issue causing calibration not to got to home position.
2025-09-17 fix bug in controller api handlers
2025-09-22 Design controller as a top connector board.
2025-09-23 fix erroneous U4 angle from 45 to 37.5
2025-09-24 rename function
2025-09-24 update output files of hardware
2025-09-27 Documentation Updates
2025-09-28 Add Flap Generator docs
2025-09-29 Update Github Pages to docs
2025-10-03 super basic one node test working for read all
2025-10-03 implement single node test for all 3 chain comm actions
2025-10-07 Add RO and WO tests
2025-10-07 Add timeout tests
2025-10-08 Start on rev2 chain com
2025-10-09 Finish Read V2
2025-10-09 Implement proper RX_HEADER state test
2025-10-15 Change firmware HAL for V7 hardware
2025-10-15 Complete Redesign of Chain Communication Protocol
2025-10-16 Fixed compile errors in master but it's still shit.
2025-10-21 Port firmware version, update and command property to new implementation.
2025-10-22 Ported all property handlers, untested
2025-10-23 Add motor control safety check for 12V power supply
2025-11-03 Reverse payload order when writing
2025-11-04 Enhance chain communication with queuing mechanism and UART callbacks
    - Added queuing support for read and write actions in the chain communication master.
    - Introduced UART callback for waiting until transmission is complete.
    - Updated synchronization logic to handle retries for property synchronization.
    - Adjusted timeout values for improved responsiveness.
    - Enhanced error logging for better debugging of module errors.
2025-11-04 Implement WRITE to BROADCAST updating
2025-11-06 Fix return codes of module prop handlers
2025-11-10 Update power specifications and connector type in architecture and controller documentation
2025-11-12 Renamed "chain comm" to "madelink" and made it into a submodule
2026-05-27 Fix erroneous offset_delta calculation for offset calibration.
2026-05-27 Update note in schematic
2026-06-16 fix: V-001 security vulnerability
    Automated security fix generated by OrbisAI Security
